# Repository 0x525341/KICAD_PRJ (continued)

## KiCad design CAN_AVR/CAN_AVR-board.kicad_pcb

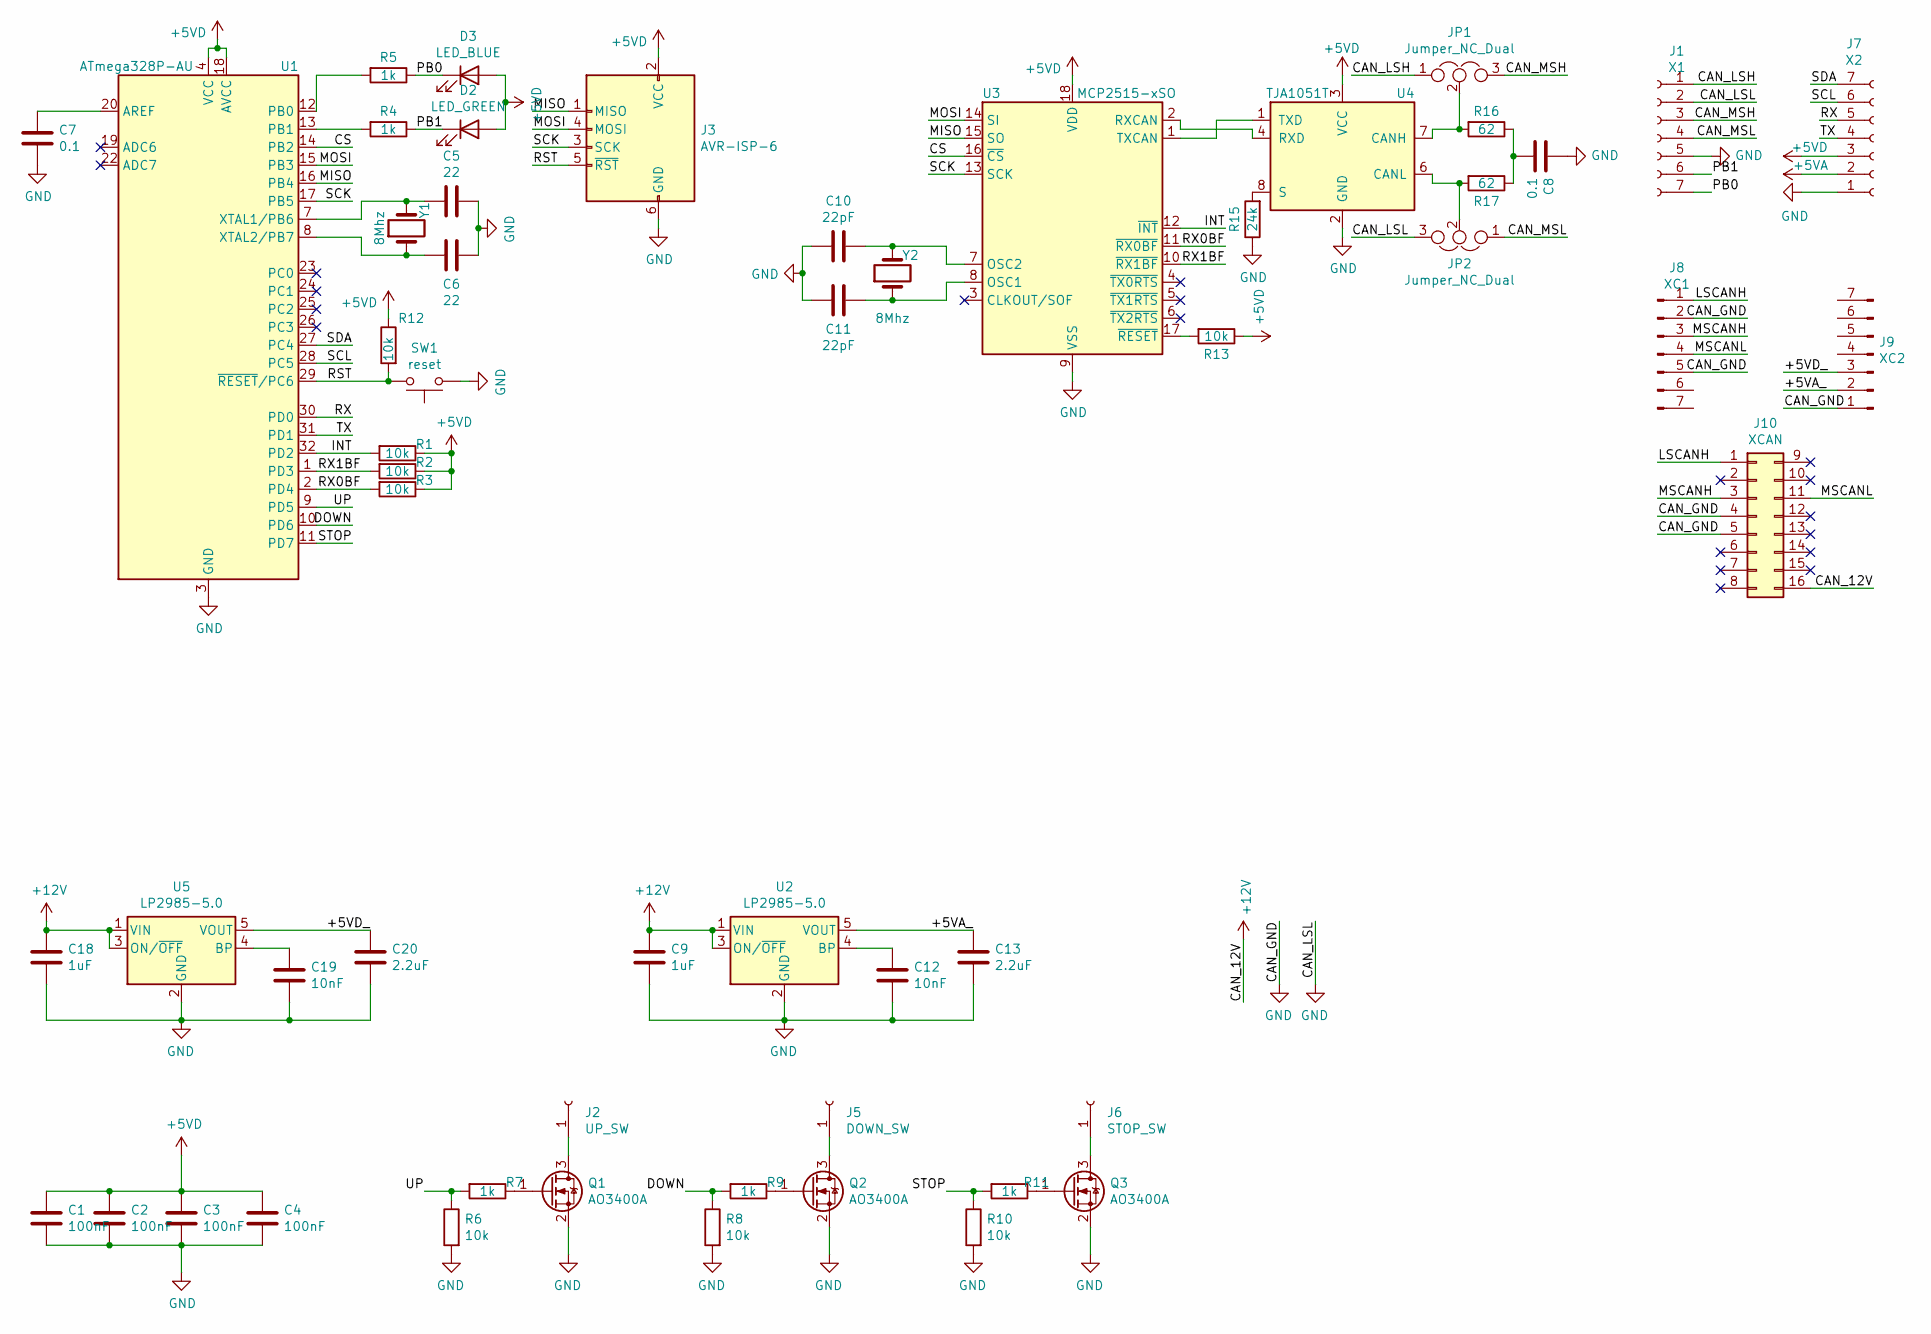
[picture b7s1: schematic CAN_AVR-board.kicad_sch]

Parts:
C1, C2, C3, C4: 100nF; C_1206_3216Metric_Pad1.33x1.80mm_HandSolder
C5, C6: 22; C_0805_2012Metric_Pad1.18x1.45mm_HandSolder
C7, C8: 0.1; C_1206_3216Metric_Pad1.33x1.80mm_HandSolder
C9, C18: 1uF; C_1206_3216Metric_Pad1.33x1.80mm_HandSolder
C10, C11: 22pF; C_0805_2012Metric_Pad1.18x1.45mm_HandSolder
C12, C19: 10nF; C_1206_3216Metric_Pad1.33x1.80mm_HandSolder
C13, C20: 2.2uF; C_1206_3216Metric_Pad1.33x1.80mm_HandSolder
D2: LED_GREEN; LED_1206_3216Metric_Pad1.42x1.75mm_HandSolder
D3: LED_BLUE; LED_1206_3216Metric_Pad1.42x1.75mm_HandSolder
J1: X1; PinHeader_1x07_P2.54mm_Vertical
J2: UP_SW; TestPoint_Keystone_5019_Minature
J3: AVR-ISP-6; PinHeader_2x03_P2.54mm_Vertical
J5: DOWN_SW; TestPoint_Keystone_5019_Minature
J6: STOP_SW; TestPoint_Keystone_5019_Minature
J7: X2; PinHeader_1x07_P2.54mm_Vertical
J8: XC1; PinSocket_1x07_P2.54mm_Vertical
J9: XC2; PinSocket_1x07_P2.54mm_Vertical
J10: XCAN; OBDII
JP1, JP2: Jumper_NC_Dual; SolderJumper-3_P2.0mm_Open_TrianglePad1.0x1.5mm_NumberLabels
Q1, Q2, Q3: AO3400A; SOT-23
R1, R2, R3, R6, R8, R10, R12, R13: 10k; R_1206_3216Metric_Pad1.30x1.75mm_HandSolder
R4, R5, R7, R9, R11: 1k; R_1206_3216Metric_Pad1.30x1.75mm_HandSolder
R15: 24k; R_1206_3216Metric_Pad1.30x1.75mm_HandSolder
R16, R17: 62; R_1206_3216Metric_Pad1.30x1.75mm_HandSolder
SW1: reset; SW_SPST_B3U-1000P
U1: ATmega328P-AU; TQFP-32_7x7mm_P0.8mm
U2, U5: LP2985-5.0; SOT-23-5
U3: MCP2515-xSO; SOIC-18W_7.5x11.6mm_P1.27mm
U4: TJA1051T; SOIC-8_3.9x4.9mm_P1.27mm
Y1, Y2: 8Mhz; Crystal_SMD_5032-2Pin_5.0x3.2mm_HandSoldering

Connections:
+5VD: C1.1, C2.1, C3.1, C4.1, D2.2 (A), D3.2 (A), J3.2 (VCC), J7.3, R1.1, R2.1, R3.1, R12.1, R13.1, U1.4 (VCC), U1.6 (VCC), U1.18 (AVCC), U3.18 (VDD), U4.3 (VCC)
+12V: C9.1, C18.1, J10.16, U2.1 (VIN), U2.3 (ON/~OFF), U5.1 (VIN), U5.3 (ON/~OFF)
/+5VA_: C13.1, J9.2, U2.5 (VOUT)
/+5VD_: C20.1, J9.3, U5.5 (VOUT)
/CAN_LSH: J1.1, JP1.1
/CAN_MSH: J1.3, JP1.3
/CAN_MSL: J1.4, JP2.1
/CS: U1.14 (PB2), U3.16 (~CS)
/DOWN: R8.1, R9.2, U1.10 (PD6)
/INT: R1.2, U1.32 (PD2), U3.12 (~INT)
/LSCANH: J8.1, J10.1
/MISO: J3.1 (MISO), U1.16 (PB4), U3.15 (SO)
/MOSI: J3.4 (MOSI), U1.15 (PB3), U3.14 (SI)
/MSCANH: J8.3, J10.3
/MSCANL: J8.4, J10.11
/PB0: D3.1 (K), J1.7, R5.1
/PB1: D2.1 (K), J1.6, R4.1
/RST: J3.5 (~RST), R12.2, SW1.1, U1.29 (~RESET/PC6)
/RX: J7.5, U1.30 (PD0)
/RX0BF: R3.2, U1.2 (PD4), U3.11 (~RX0BF)
/RX1BF: R2.2, U1.1 (PD3), U3.10 (~RX1BF)
/SCK: J3.3 (SCK), U1.17 (PB5), U3.13 (SCK)
/SCL: J7.6, U1.28 (PC5)
/SDA: J7.7, U1.27 (PC4)
/STOP: R10.1, R11.2, U1.11 (PD7)
/TX: J7.4, U1.31 (PD1)
/UP: R6.1, R7.2, U1.9 (PD5)
GND: C1.2, C2.2, C3.2, C4.2, C5.2, C6.2, C7.2, C8.1, C9.2, C10.1, C11.1, C12.2, C13.2, C18.2, C19.2, C20.2, J1.2, J1.5, J3.6 (GND), J7.1, J8.2, J8.5, J9.1, J10.4, J10.5, JP2.3, Q1.2 (S), Q2.2 (S), Q3.2 (S), R6.2, R8.2, R10.2, R15.1, SW1.2, U1.3 (GND), U1.5 (GND), U1.21 (GND), U2.2 (GND), U3.9 (VSS), U4.2 (GND), U5.2 (GND)
unnamed: C5.1, U1.7 (XTAL1/PB6), Y1.2
unnamed: C6.1, U1.8 (XTAL2/PB7), Y1.1
unnamed: C7.1, U1.20 (AREF)
unnamed: C8.2, R16.1, R17.1
unnamed: C10.2, U3.7 (OSC2), Y2.2
unnamed: C11.2, U3.8 (OSC1), Y2.1
unnamed: C12.1, U2.4 (BP)
unnamed: C19.1, U5.4 (BP)
unnamed: J2.1, Q1.3 (D)
unnamed: J5.1, Q2.3 (D)
unnamed: J6.1, Q3.3 (D)
unnamed: JP1.2, R16.2, U4.7 (CANH)
unnamed: JP2.2, R17.2, U4.6 (CANL)
unnamed: Q1.1 (G), R7.1
unnamed: Q2.1 (G), R9.1
unnamed: Q3.1 (G), R11.1
unnamed: R4.2, U1.13 (PB1)
unnamed: R5.2, U1.12 (PB0)
unnamed: R13.2, U3.17 (~RESET)
unnamed: R15.2, U4.8 (S)
unnamed: U3.1 (TXCAN), U4.1 (TXD)
unnamed: U3.2 (RXCAN), U4.4 (RXD)

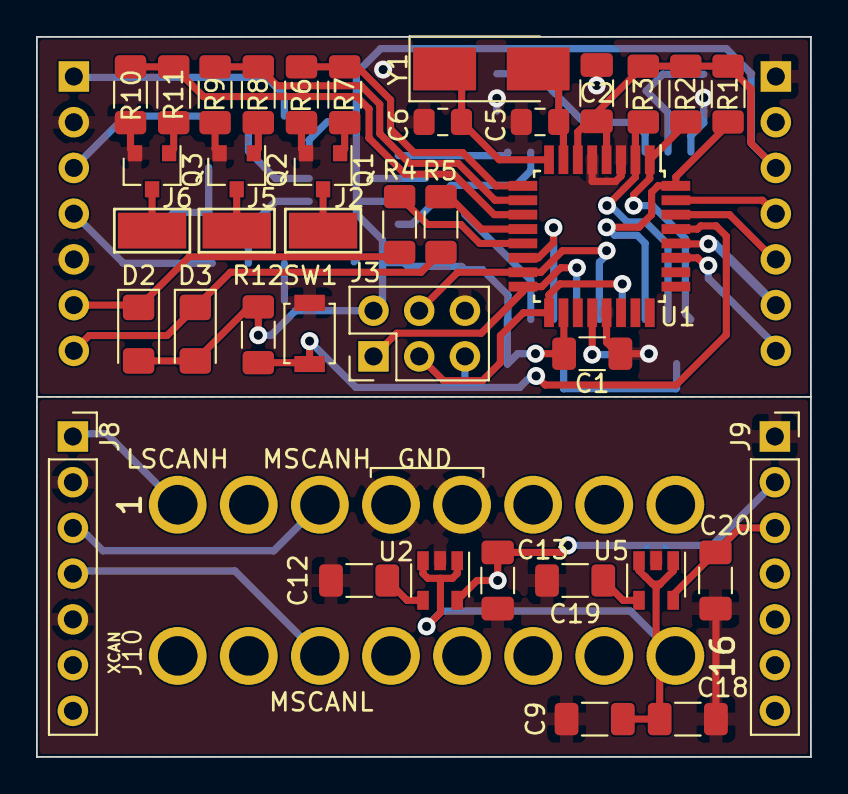
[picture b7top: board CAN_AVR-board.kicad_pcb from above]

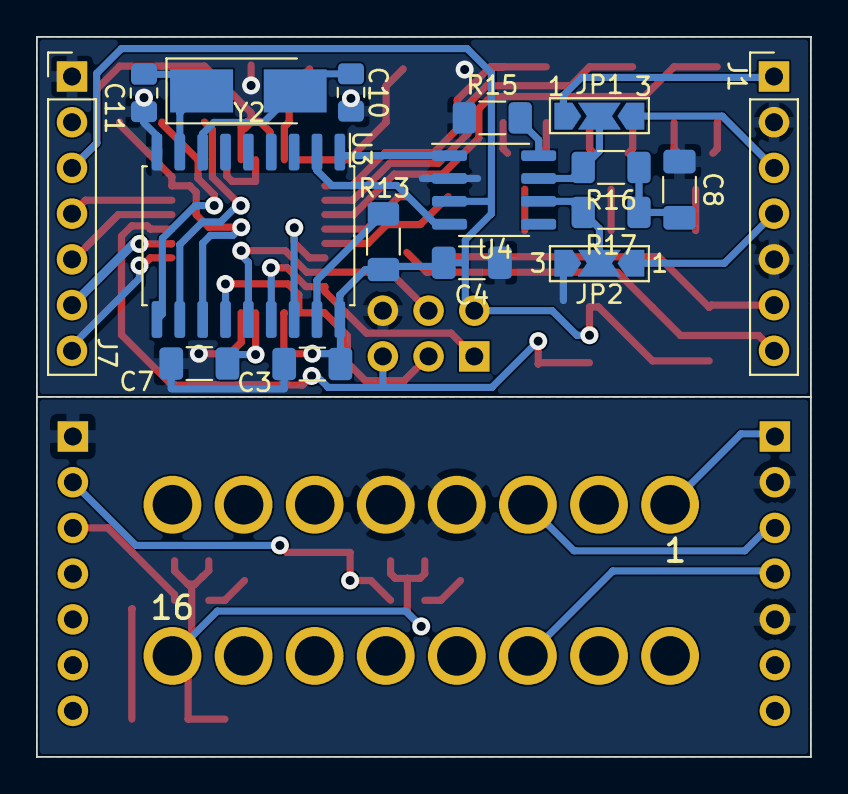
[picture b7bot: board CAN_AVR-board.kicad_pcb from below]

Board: 2 copper layers, 43.0 x 40.0 mm, 56 parts (17 on the bottom side), 50 nets.
